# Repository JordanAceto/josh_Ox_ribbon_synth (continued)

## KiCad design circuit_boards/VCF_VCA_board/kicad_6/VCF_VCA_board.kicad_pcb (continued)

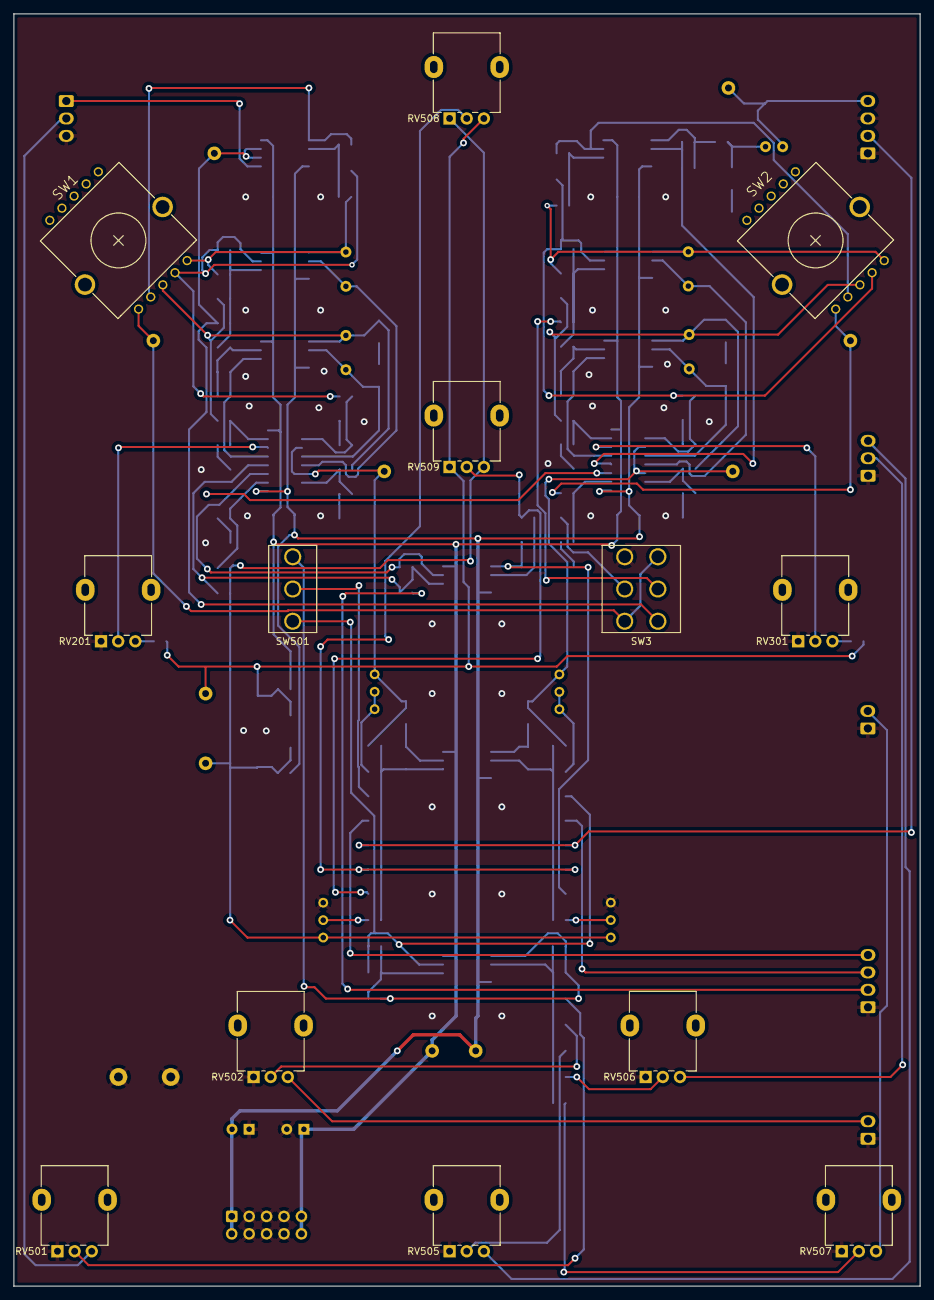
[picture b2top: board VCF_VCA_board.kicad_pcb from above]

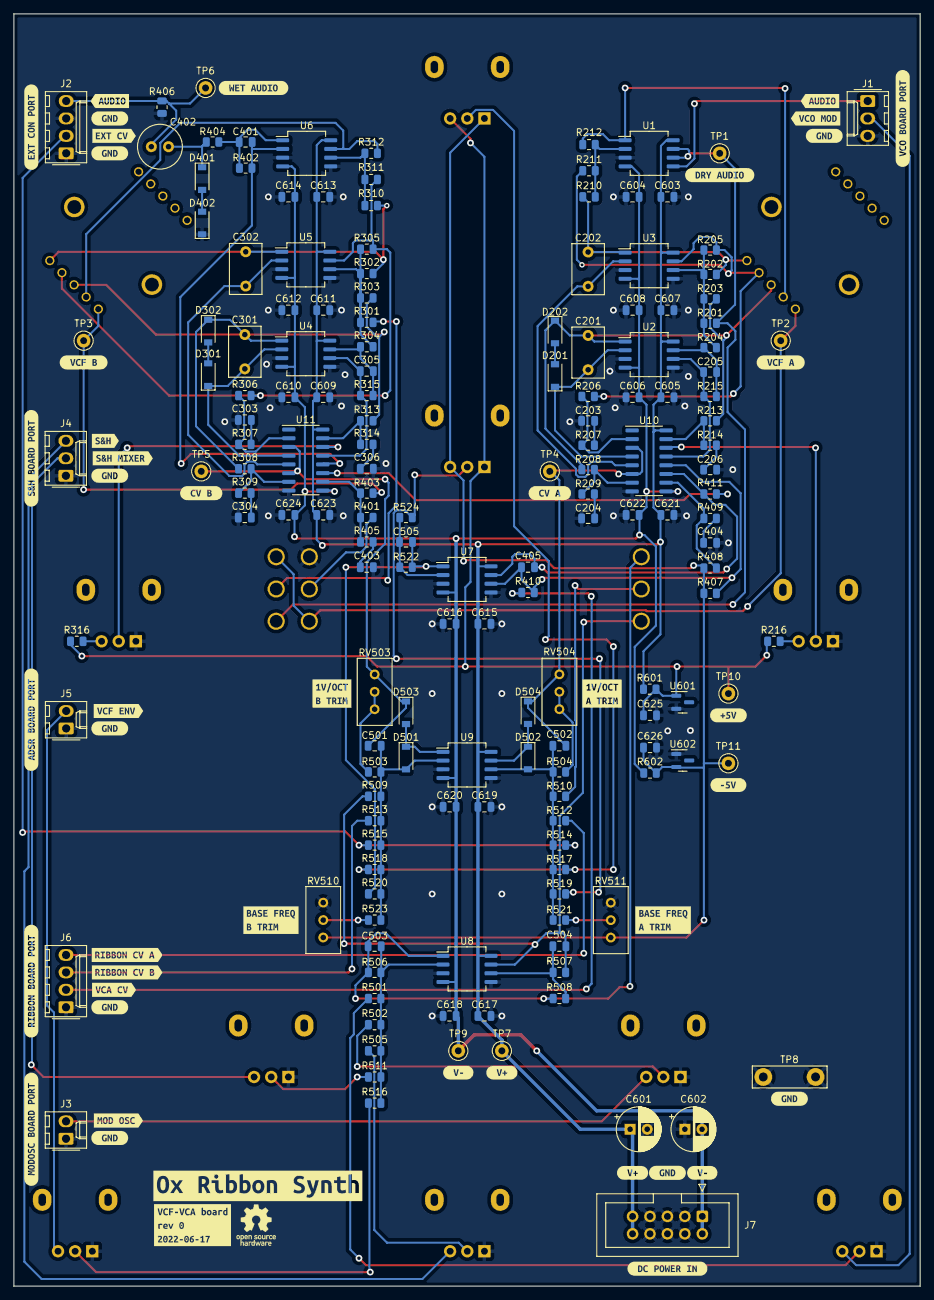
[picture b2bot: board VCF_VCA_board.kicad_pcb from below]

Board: 2 copper layers, 132.1 x 185.4 mm, 220 parts (207 on the bottom side), 94 nets.

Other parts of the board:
C301, C302: 220p; C_Rect_L7.2mm_W4.5mm_P5.00mm_FKS2_FKP2_MKS2_MKP2
C303, C304, C306: 1n2; C_0805_2012Metric
C305: 10p; C_0805_2012Metric
D301, D302: 5v1; D_SOD-123
R301, R302, R304, R305, R306, R308, R310, R311, R312, R315: 30k; R_0805_2012Metric
R303: 390k; R_0805_2012Metric
R307, R309, R314: 220; R_0805_2012Metric
R313: 15k; R_0805_2012Metric
R316: 18k; R_0805_2012Metric
RV301: 10k; Potentiometer_Alpha_RD901F-40-00D_Single_Vertical
kibuzzard-62AC7A9F: G***; kibuzzard-62AC7A9F
kibuzzard-62AC8A1C: G***; kibuzzard-62AC8A1C
kibuzzard-62AC8A2D: G***; kibuzzard-62AC8A2D
kibuzzard-62AC8A4C: G***; kibuzzard-62AC8A4C
kibuzzard-62AC8A9A: G***; kibuzzard-62AC8A9A
kibuzzard-62AC8A40: G***; kibuzzard-62AC8A40
kibuzzard-62AC8A61: G***; kibuzzard-62AC8A61
kibuzzard-62AC8A72: G***; kibuzzard-62AC8A72
kibuzzard-62AC8A87: G***; kibuzzard-62AC8A87
kibuzzard-62AC8B01: G***; kibuzzard-62AC8B01
kibuzzard-62AC8B2D: G***; kibuzzard-62AC8B2D
kibuzzard-62AC8B15: G***; kibuzzard-62AC8B15
kibuzzard-62AC8B47: G***; kibuzzard-62AC8B47
kibuzzard-62AC78CB: G***; kibuzzard-62AC78CB
kibuzzard-62AC88AD: G***; kibuzzard-62AC88AD
kibuzzard-62AC88C6: G***; kibuzzard-62AC88C6
kibuzzard-62AC88DA: G***; kibuzzard-62AC88DA
kibuzzard-62AC88EB: G***; kibuzzard-62AC88EB
kibuzzard-62AC89A8: G***; kibuzzard-62AC89A8
kibuzzard-62AC89C0: G***; kibuzzard-62AC89C0
kibuzzard-62AC89D1: G***; kibuzzard-62AC89D1
kibuzzard-62AC89EA: G***; kibuzzard-62AC89EA
kibuzzard-62AC755C, kibuzzard-62AC755C#2, kibuzzard-62AC755C#3, kibuzzard-62AC755C#4, kibuzzard-62AC755C#5, kibuzzard-62AC755C#6, kibuzzard-62AC755C#7, kibuzzard-62AC755C#8, kibuzzard-62AC755C#9: G***; kibuzzard-62AC755C
kibuzzard-62AC791A, kibuzzard-62AC791A#2: G***; kibuzzard-62AC791A
kibuzzard-62AC792A, kibuzzard-62AC792A#2: G***; kibuzzard-62AC792A
kibuzzard-62AC886F: G***; kibuzzard-62AC886F
kibuzzard-62AC887D: G***; kibuzzard-62AC887D
kibuzzard-62AC892A, kibuzzard-62AC892A#2: G***; kibuzzard-62AC892A
kibuzzard-62AC8760: G***; kibuzzard-62AC8760
kibuzzard-62AC8892: G***; kibuzzard-62AC8892
kibuzzard-62AC8908: G***; kibuzzard-62AC8908
kibuzzard-62AC8951: G***; kibuzzard-62AC8951
kibuzzard-62AC8974: G***; kibuzzard-62AC8974
kibuzzard-62AC8994: G***; kibuzzard-62AC8994

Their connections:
+5V REF: R316.1; also elsewhere on the board
/SVF_B/BP_OUT: C301.2, D302.1 (K), R303.2, R308.1, R313.2; also elsewhere on the board
/SVF_B/HP_OUT: R305.2, R306.1, R311.1; also elsewhere on the board
/SVF_B/LP_OUT: C302.2, R302.2, R310.1; also elsewhere on the board
/SVF_B/NOTCH_OUT: R312.2; also elsewhere on the board
/SVF_B/SIGNAL_IN: R301.1; also elsewhere on the board
unnamed 35: C301.1, D301.1 (K); also elsewhere on the board
unnamed 36: C302.1; also elsewhere on the board
unnamed: C303.1, R307.2
unnamed: C304.1, R309.2
unnamed 39: C305.1, R304.2, R315.2; also elsewhere on the board
unnamed 40: C305.2, R315.1; also elsewhere on the board
unnamed: C306.1, R314.2
unnamed: D301.2 (A), D302.2 (A)
unnamed 69: R301.2, R302.1, R303.1, R304.1, R305.1; also elsewhere on the board
unnamed 70: R306.2, R307.1; also elsewhere on the board
unnamed 71: R308.2, R309.1; also elsewhere on the board
unnamed 72: R310.2, R311.2, R312.1; also elsewhere on the board
unnamed 73: R313.1, R314.1; also elsewhere on the board
unnamed: R316.2, RV301.3
unnamed 91: RV301.2; also elsewhere on the board

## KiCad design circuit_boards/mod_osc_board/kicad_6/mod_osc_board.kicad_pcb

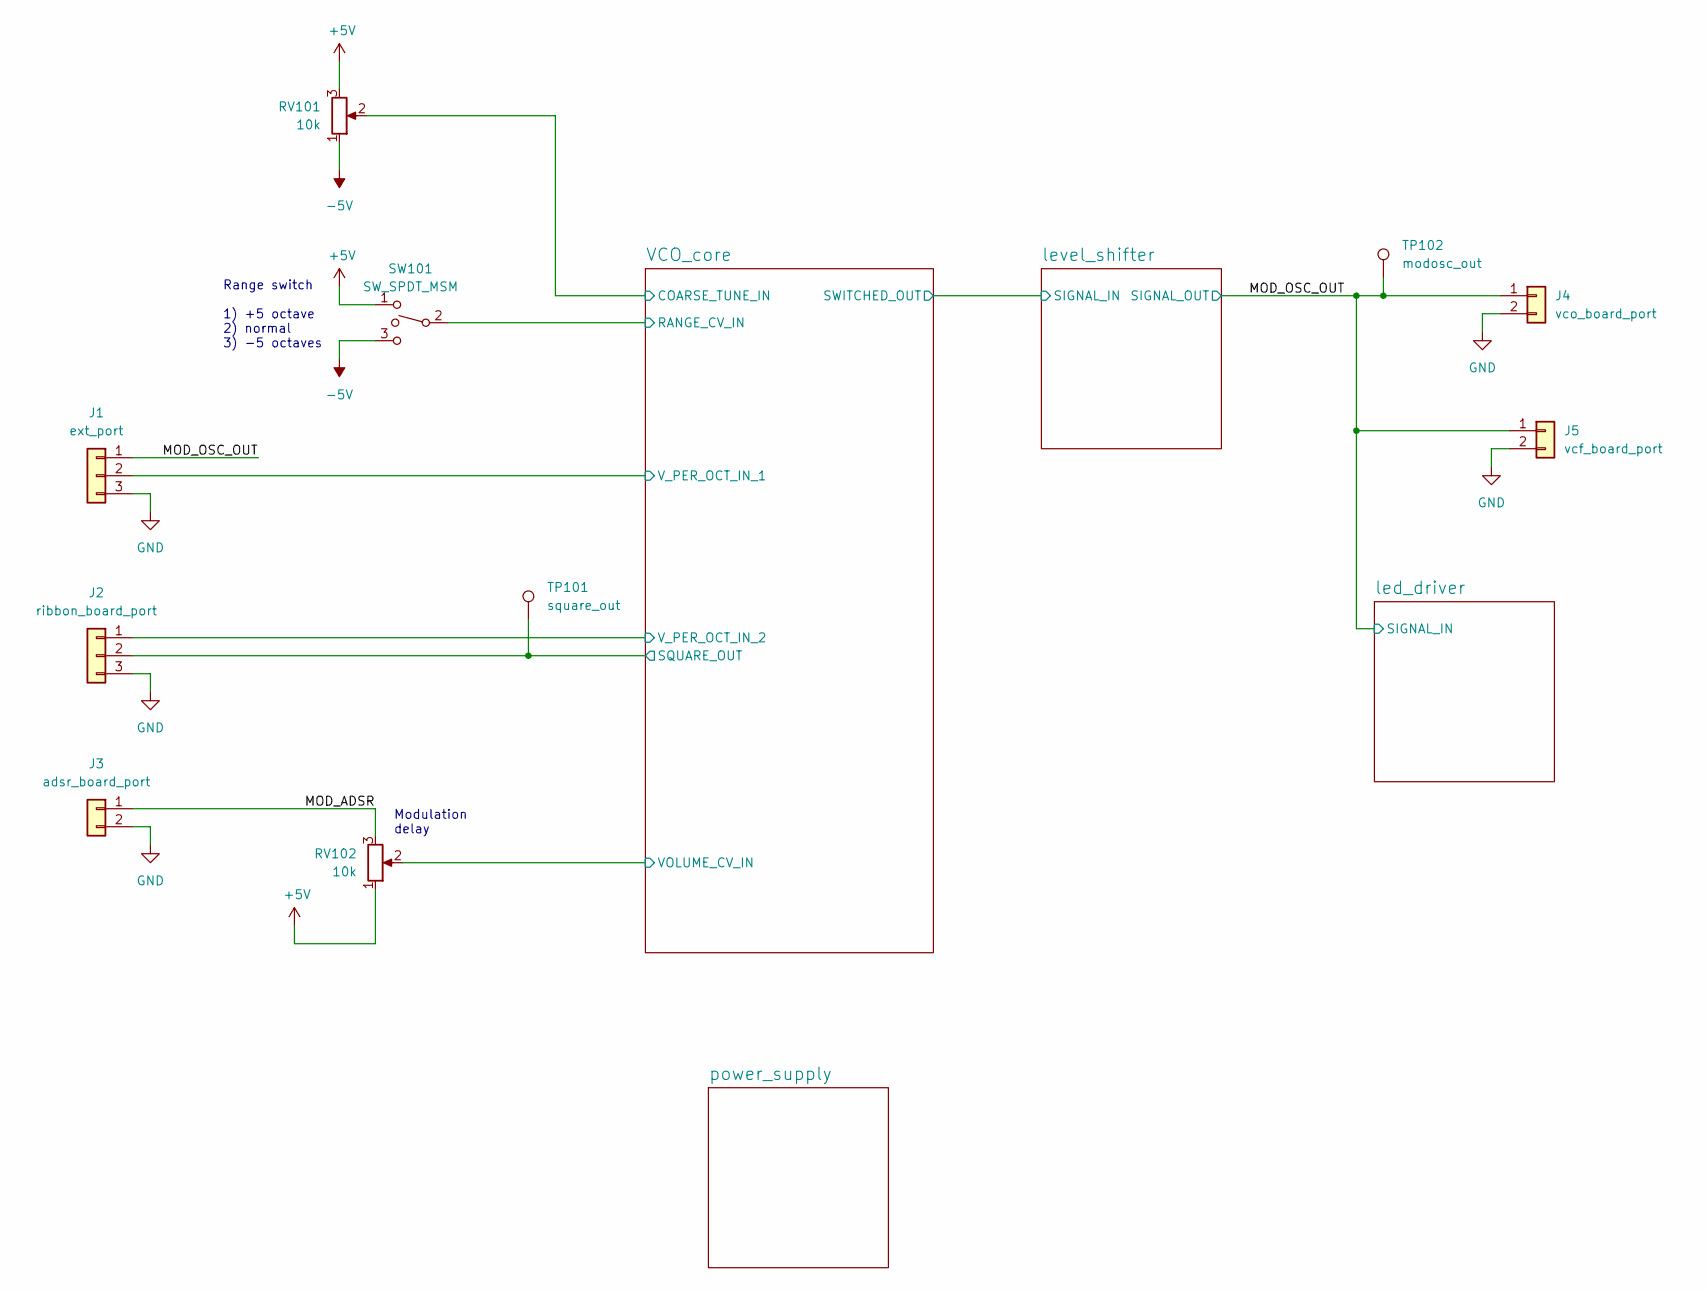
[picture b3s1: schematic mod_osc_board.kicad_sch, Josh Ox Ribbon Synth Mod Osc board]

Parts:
J1: ext_port; Molex_KK-254_AE-6410-03A_1x03_P2.54mm_Vertical
J2: ribbon_board_port; Molex_KK-254_AE-6410-03A_1x03_P2.54mm_Vertical
J3: adsr_board_port; Molex_KK-254_AE-6410-02A_1x02_P2.54mm_Vertical
J4: vco_board_port; Molex_KK-254_AE-6410-02A_1x02_P2.54mm_Vertical
J5: vcf_board_port; Molex_KK-254_AE-6410-02A_1x02_P2.54mm_Vertical
RV101, RV102: 10k; Potentiometer_P260T
SW101: SW_SPDT_MSM; SPDT_mini_toggle
TP101: square_out; TestPoint_Keystone_5000-5004_Miniature
TP102: modosc_out; TestPoint_Keystone_5000-5004_Miniature

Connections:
+5V: RV101.3, RV102.1, SW101.1; also elsewhere on the board
-5V: RV101.1, SW101.3; also elsewhere on the board
/MOD_ADSR: J3.1, RV102.3
/MOD_OSC_OUT: J1.1, J4.1, J5.1, TP102.1; also elsewhere on the board
/VCO_core/COARSE_TUNE_IN: RV101.2; also elsewhere on the board
/VCO_core/RANGE_CV_IN: SW101.2; also elsewhere on the board
/VCO_core/SQUARE_OUT: J2.2, TP101.1; also elsewhere on the board
/VCO_core/VOLUME_CV_IN: RV102.2; also elsewhere on the board
/VCO_core/V_PER_OCT_IN_1: J1.2; also elsewhere on the board
/VCO_core/V_PER_OCT_IN_2: J2.1; also elsewhere on the board

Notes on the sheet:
Range switch 1) +5 octave 2) normal 3) -5 octaves
Modulation delay

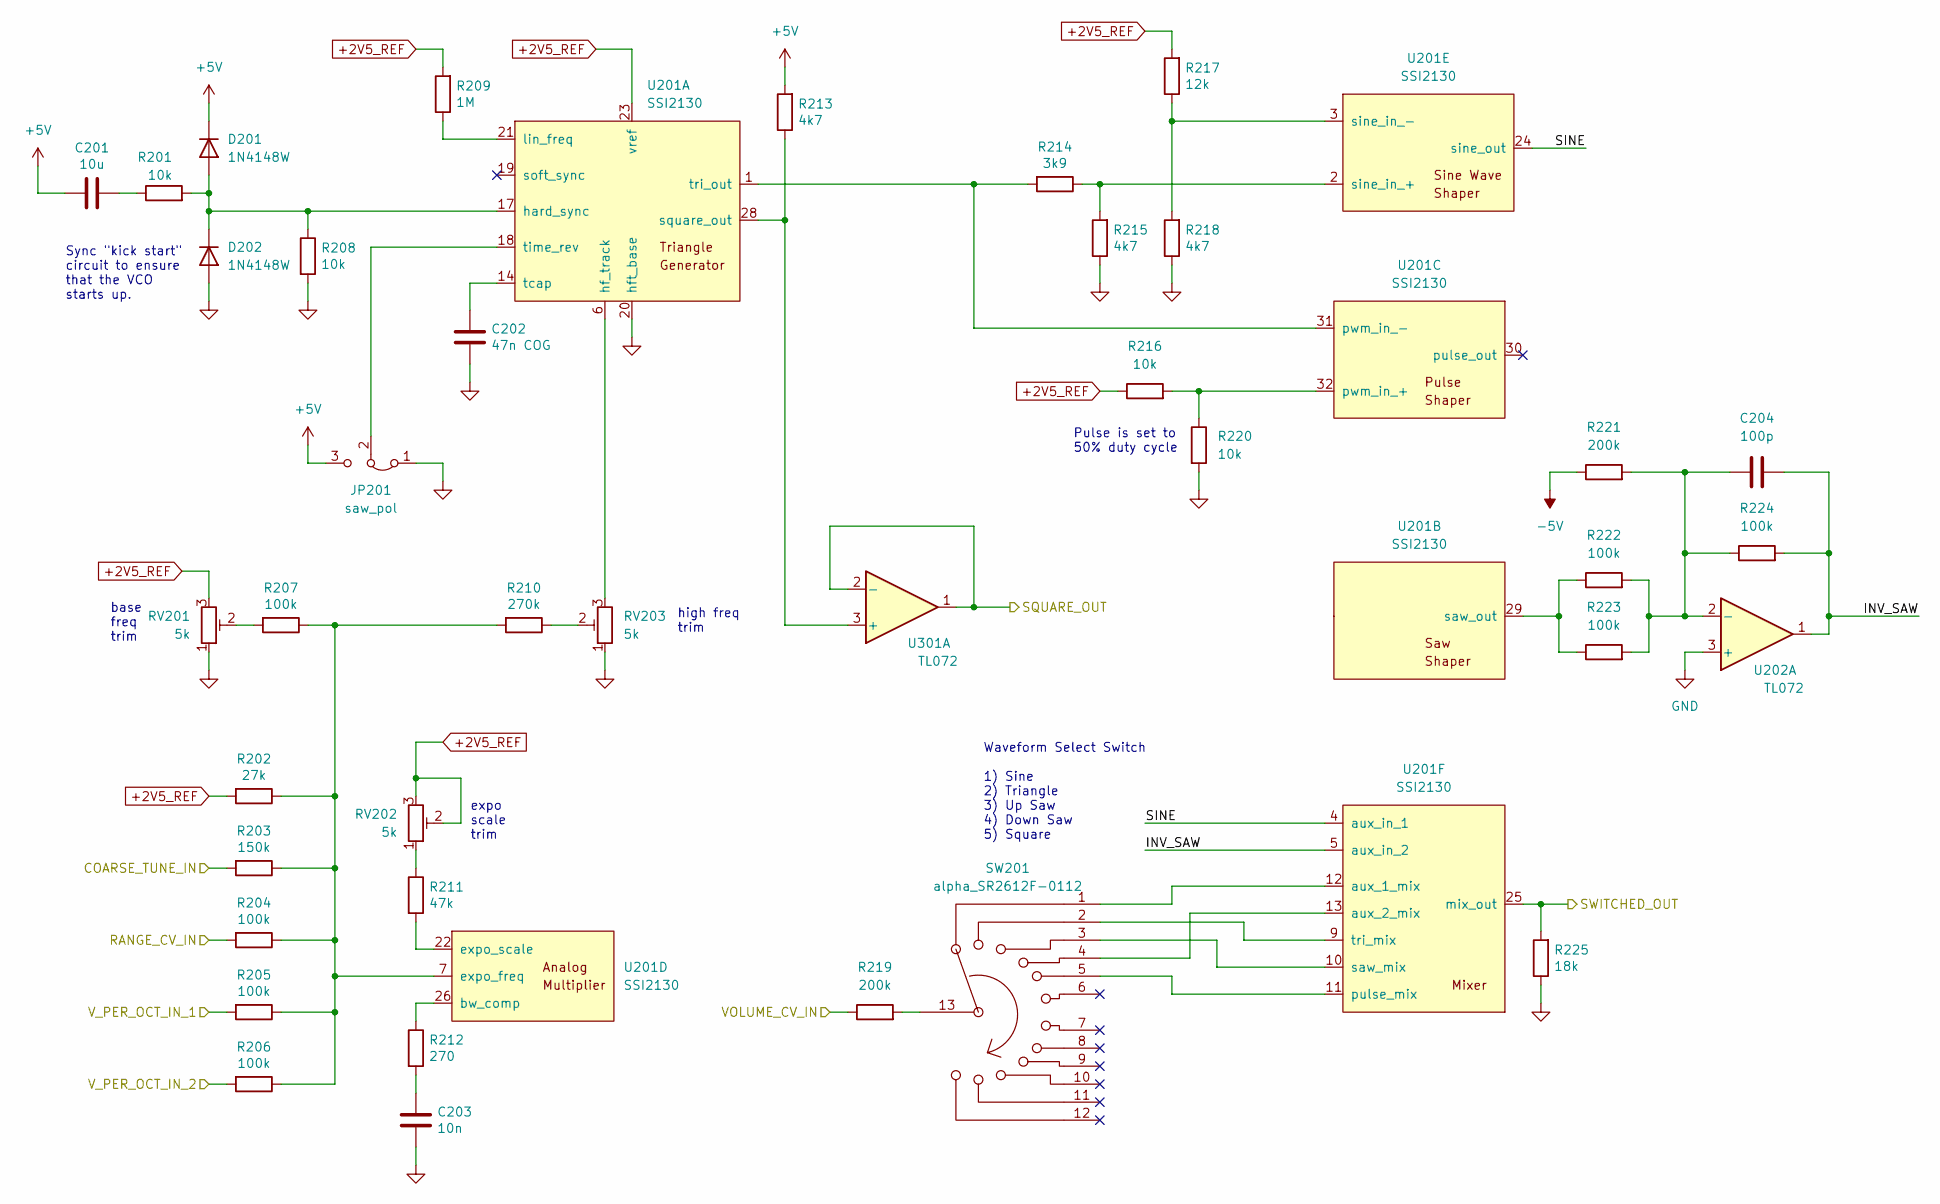
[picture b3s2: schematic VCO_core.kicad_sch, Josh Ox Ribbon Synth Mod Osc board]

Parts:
C201: 10u; C_0805_2012Metric
C202: 47n COG; C_0805_2012Metric
C203: 10n; C_0805_2012Metric
C204: 100p; C_0805_2012Metric
D201, D202: 1N4148W; D_SOD-123
JP201: saw_pol; SolderJumper-3_P1.3mm_Bridged12_RoundedPad1.0x1.5mm
R201, R208, R216, R220: 10k; R_0805_2012Metric
R202: 27k; R_0805_2012Metric
R203: 150k; R_0805_2012Metric
R204, R205, R206, R207, R222, R223, R224: 100k; R_0805_2012Metric
R209: 1M; R_0805_2012Metric
R210: 270k; R_0805_2012Metric
R211: 47k; R_0805_2012Metric
R212: 270; R_0805_2012Metric
R213, R215, R218: 4k7; R_0805_2012Metric
R214: 3k9; R_0805_2012Metric
R217: 12k; R_0805_2012Metric
R219, R221: 200k; R_0805_2012Metric
R225: 18k; R_0805_2012Metric
RV201, RV202, RV203: 5k; Potentiometer_Bourns_3296W_Vertical
SW201: alpha_SR2612F-0112; apha_SR2612F-0112
U201: SSI2130; PQN32_HandSoldering
U202, U301: TL072; SO-8_5.3x6.2mm_P1.27mm

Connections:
+2V5_REF: R202.2, R209.2, R216.1, R217.2, RV201.3, RV202.2, RV202.3, U201.23 (vref); also elsewhere on the board
+5V: C201.2, D201.1 (K), JP201.3 (B), R213.2; also elsewhere on the board
-5V: R221.1; also elsewhere on the board
/VCO_core/COARSE_TUNE_IN: R203.2; also elsewhere on the board
/VCO_core/INV_SAW: C204.2, R224.2, U201.5 (aux_in_2), U202.1
/VCO_core/RANGE_CV_IN: R204.2; also elsewhere on the board
/VCO_core/SINE: U201.4 (aux_in_1), U201.24 (sine_out)
/VCO_core/SQUARE_OUT: U301.1, U301.2 (-); also elsewhere on the board
/VCO_core/SWITCHED_OUT: R225.2, U201.25 (mix_out); also elsewhere on the board
/VCO_core/VOLUME_CV_IN: R219.1; also elsewhere on the board
/VCO_core/V_PER_OCT_IN_1: R205.2; also elsewhere on the board
/VCO_core/V_PER_OCT_IN_2: R206.2; also elsewhere on the board
unnamed: C201.1, R201.1
unnamed: C202.1, U201.14 (tcap)
unnamed: C203.1, R212.2
unnamed: C204.1, R221.2, R222.2, R223.2, R224.1, U202.2 (-)
unnamed: D201.2 (A), D202.1 (K), R201.2, R208.1, U201.17 (hard_sync)
unnamed: JP201.2 (C), U201.18 (time_rev)
unnamed: R202.1, R203.1, R204.1, R205.1, R206.1, R207.1, R210.2, U201.7 (expo_freq)
unnamed: R207.2, RV201.2
unnamed: R209.1, U201.21 (lin_freq)
unnamed: R210.1, RV203.2
unnamed: R211.1, RV202.1
unnamed: R211.2, U201.22 (expo_scale)
unnamed: R212.1, U201.26 (bw_comp)
unnamed: R213.1, U201.28 (square_out), U301.3 (+)
unnamed: R214.1, R215.2, U201.2 (sine_in_+)
unnamed: R214.2, U201.1 (tri_out), U201.31 (pwm_in_-)
unnamed: R216.2, R220.1, U201.32 (pwm_in_+)
unnamed: R217.1, R218.2, U201.3 (sine_in_-)
unnamed: R219.2, SW201.13
unnamed: R222.1, R223.1, U201.29 (saw_out)
unnamed: RV203.3, U201.6 (hf_track)
unnamed: SW201.1, U201.12 (aux_1_mix)
unnamed: SW201.2, U201.9 (tri_mix)
unnamed: SW201.3, U201.10 (saw_mix)
unnamed: SW201.4, U201.13 (aux_2_mix)
unnamed: SW201.5, U201.11 (pulse_mix)

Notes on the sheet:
Waveform Select Switch 1) Sine 2) Triangle 3) Up Saw 4) Down Saw 5) Square
high freq trim
Pulse is set to 50% duty cycle
expo scale trim
Sync "kick start" circuit to ensure that the VCO starts up.
base freq trim

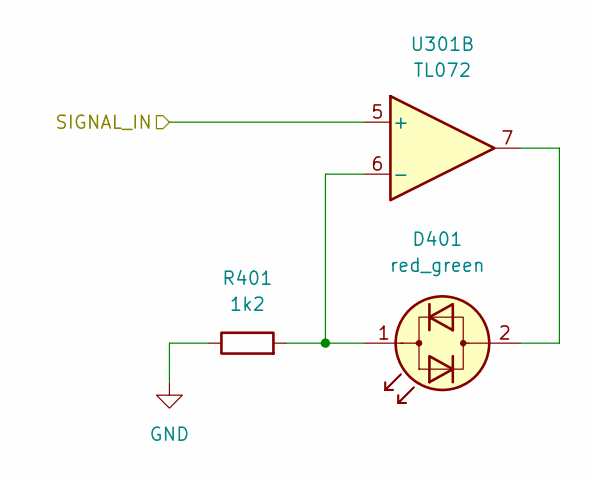
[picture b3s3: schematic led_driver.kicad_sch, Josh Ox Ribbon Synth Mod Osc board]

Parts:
D401: red_green; LED_D5.0mm
R401: 1k2; R_0805_2012Metric
U301: TL072; SO-8_5.3x6.2mm_P1.27mm

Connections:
/MOD_OSC_OUT: U301.5 (+); also elsewhere on the board
unnamed 22: D401.1 (KA), R401.2, U301.6 (-); also elsewhere on the board
unnamed 23: D401.2 (AK), U301.7; also elsewhere on the board

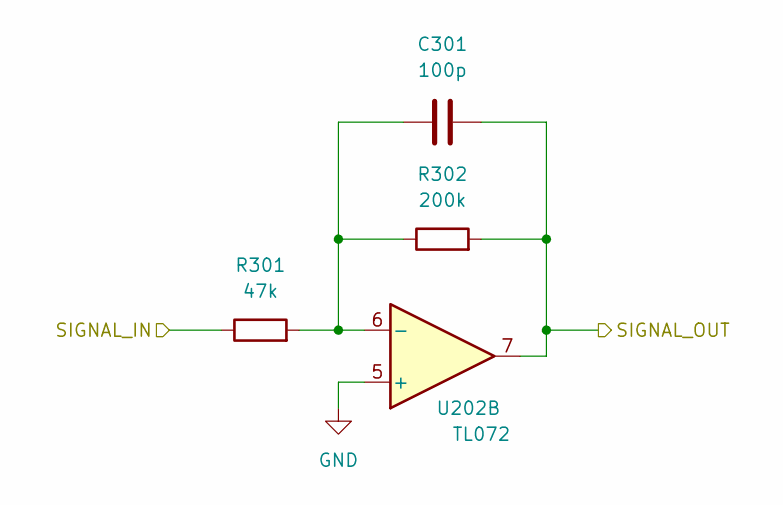
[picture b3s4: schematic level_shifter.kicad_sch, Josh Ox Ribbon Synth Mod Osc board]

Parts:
C301: 100p; C_0805_2012Metric
R301: 47k; R_0805_2012Metric
R302: 200k; R_0805_2012Metric
U202: TL072; SO-8_5.3x6.2mm_P1.27mm

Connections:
/MOD_OSC_OUT: C301.2, R302.2, U202.7; also elsewhere on the board
/VCO_core/SWITCHED_OUT: R301.1; also elsewhere on the board
unnamed: C301.1, R301.2, R302.1, U202.6 (-)

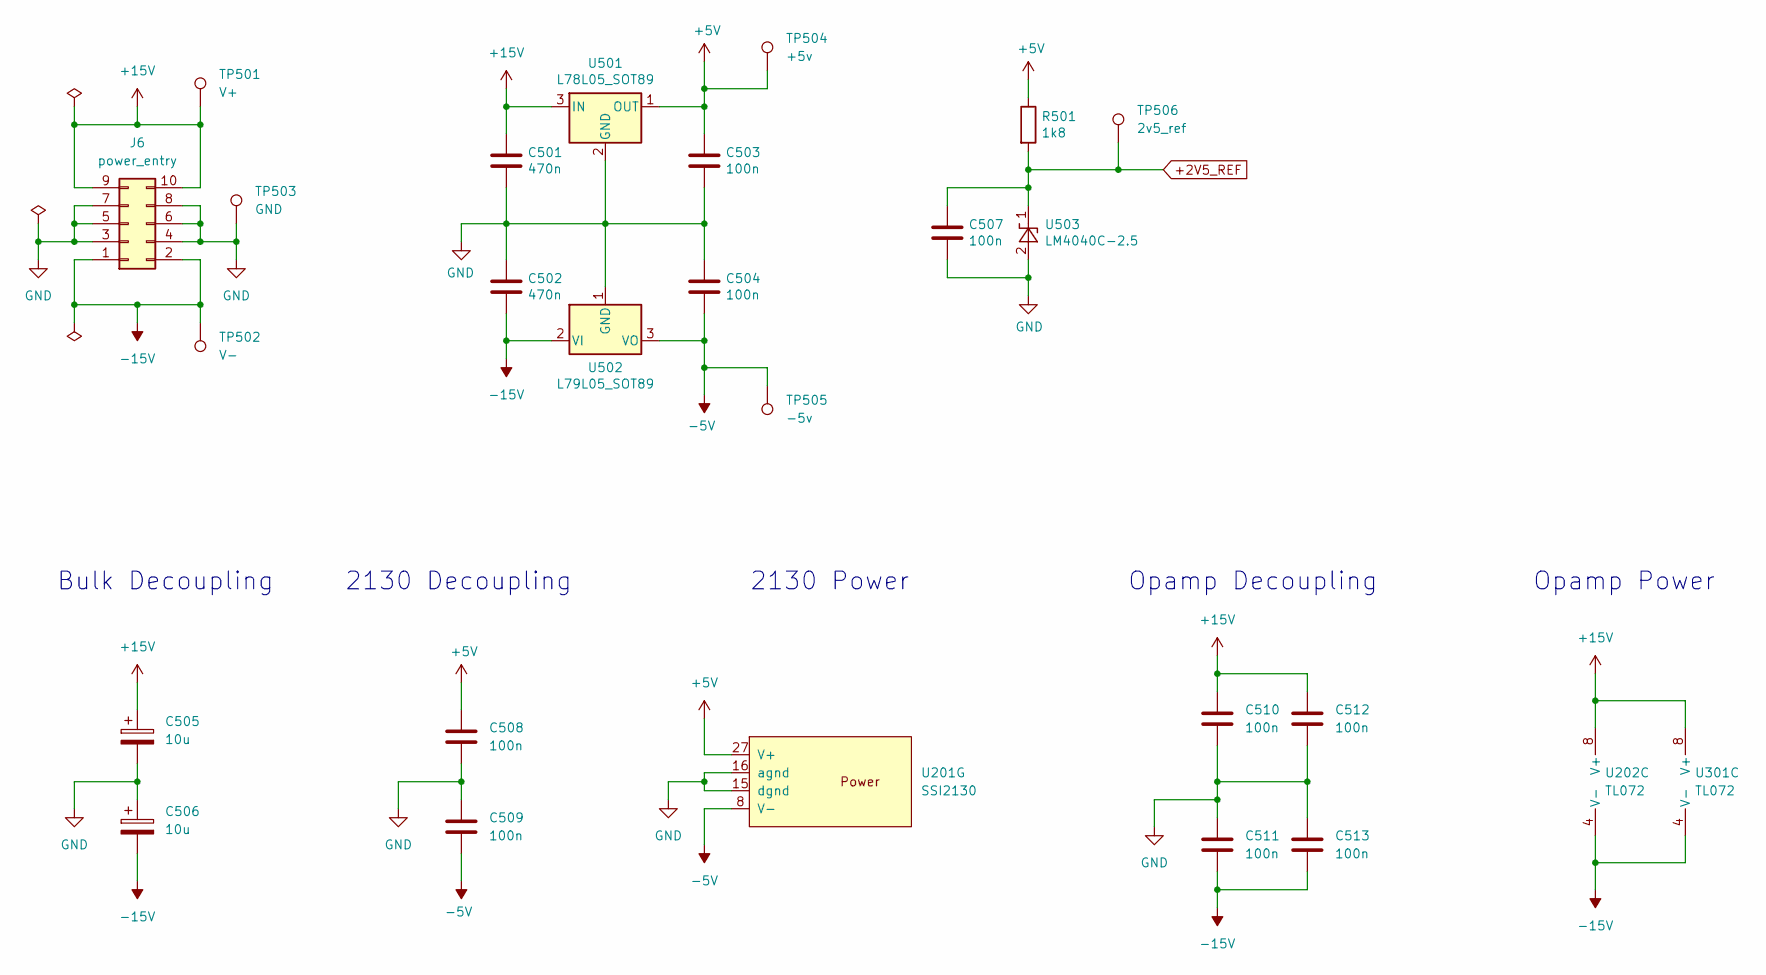
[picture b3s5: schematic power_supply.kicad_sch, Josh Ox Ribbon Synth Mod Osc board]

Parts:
C501, C502: 470n; C_0805_2012Metric
C503, C504, C507, C508, C509, C510, C511, C512, C513: 100n; C_0805_2012Metric
C505, C506: 10u; CP_Radial_D6.3mm_P2.50mm
J6: power_entry; IDC-Header_2x05_P2.54mm_Vertical
R501: 1k8; R_0805_2012Metric
TP501: V+; TestPoint_Keystone_5000-5004_Miniature
TP502: V-; TestPoint_Keystone_5000-5004_Miniature
TP503: GND; TestPoint_Bridge_Pitch7.62mm_Drill1.3mm
TP504: +5v; TestPoint_Keystone_5000-5004_Miniature
TP505: -5v; TestPoint_Keystone_5000-5004_Miniature
TP506: 2v5_ref; TestPoint_Keystone_5000-5004_Miniature
U201: SSI2130; PQN32_HandSoldering
U202, U301: TL072; SO-8_5.3x6.2mm_P1.27mm
U501: L78L05_SOT89; SOT-89-3
U502: L79L05_SOT89; SOT-89-3
U503: LM4040C-2.5; SOT-23

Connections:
+2V5_REF: C507.1, R501.2, TP506.1, U503.1 (K); also elsewhere on the board
+5V: C503.1, C508.1, R501.1, TP504.1, U201.27 (V+), U501.1 (OUT); also elsewhere on the board
+15V: C501.1, C505.1, C510.1, C512.1, J6.9, J6.10, TP501.1, U202.8 (V+), U301.8 (V+), U501.3 (IN)
-5V: C504.2, C509.2, TP505.1, U201.8 (V-), U502.3 (VO); also elsewhere on the board
-15V: C502.2, C506.2, C511.2, C513.2, J6.1, J6.2, TP502.1, U202.4 (V-), U301.4 (V-), U502.2 (VI)

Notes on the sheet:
2130 Decoupling
Opamp Decoupling
2130 Power
Opamp Power
Bulk Decoupling

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
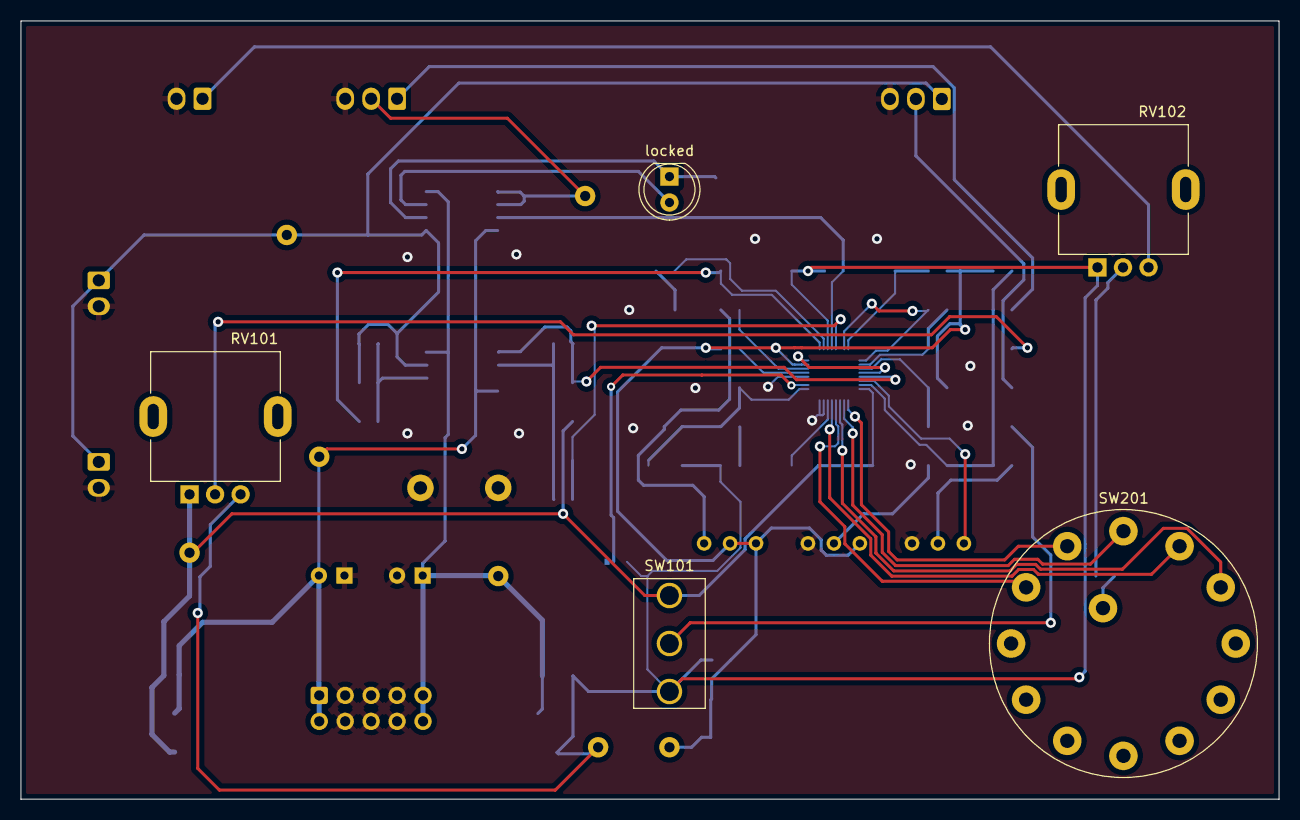
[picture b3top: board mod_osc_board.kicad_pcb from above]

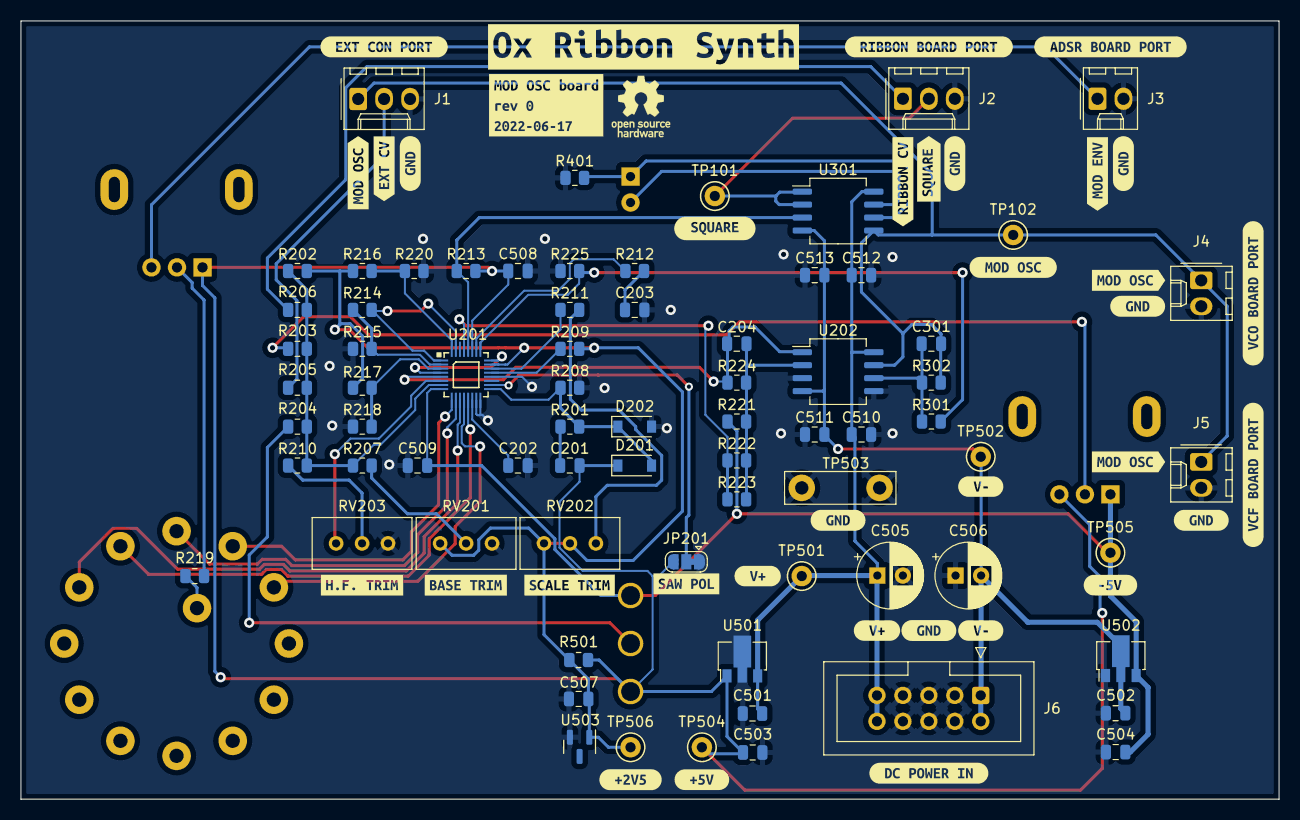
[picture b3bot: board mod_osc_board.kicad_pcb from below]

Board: 2 copper layers, 123.2 x 76.2 mm, 113 parts (108 on the bottom side), 46 nets.

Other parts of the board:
kibuzzard-62AC7A9F: G***; kibuzzard-62AC7A9F
kibuzzard-62AC7C76, kibuzzard-62AC7C76#2, kibuzzard-62AC7C76#3: G***; kibuzzard-62AC7C76
kibuzzard-62AC7CCE: G***; kibuzzard-62AC7CCE
kibuzzard-62AC7CEB: G***; kibuzzard-62AC7CEB
kibuzzard-62AC7D00: G***; kibuzzard-62AC7D00
kibuzzard-62AC7D1D: G***; kibuzzard-62AC7D1D
kibuzzard-62AC7D8B: G***; kibuzzard-62AC7D8B
kibuzzard-62AC7D30: G***; kibuzzard-62AC7D30
kibuzzard-62AC7D44: G***; kibuzzard-62AC7D44
kibuzzard-62AC7D55: G***; kibuzzard-62AC7D55
kibuzzard-62AC7D68: G***; kibuzzard-62AC7D68
kibuzzard-62AC7D79: G***; kibuzzard-62AC7D79
kibuzzard-62AC7DA9: G***; kibuzzard-62AC7DA9
kibuzzard-62AC7DB6: G***; kibuzzard-62AC7DB6
kibuzzard-62AC7DF7: G***; kibuzzard-62AC7DF7
kibuzzard-62AC7EA8: G***; kibuzzard-62AC7EA8
kibuzzard-62AC7EE1: G***; kibuzzard-62AC7EE1
kibuzzard-62AC7EFA: G***; kibuzzard-62AC7EFA
kibuzzard-62AC7F0B: G***; kibuzzard-62AC7F0B
kibuzzard-62AC78CB: G***; kibuzzard-62AC78CB
kibuzzard-62AC755C, kibuzzard-62AC755C#2, kibuzzard-62AC755C#3, kibuzzard-62AC755C#4, kibuzzard-62AC755C#5, kibuzzard-62AC755C#6, kibuzzard-62AC755C#7: G***; kibuzzard-62AC755C
kibuzzard-62AC791A, kibuzzard-62AC791A#2: G***; kibuzzard-62AC791A
kibuzzard-62AC792A, kibuzzard-62AC792A#2: G***; kibuzzard-62AC792A
kibuzzard-62AC911A: G***; kibuzzard-62AC911A
kibuzzard-62ACB089: G***; kibuzzard-62ACB089
locked: red_green; LED_D5.0mm

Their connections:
unnamed 22: locked.1 (KA); also elsewhere on the board
unnamed 23: locked.2 (AK); also elsewhere on the board

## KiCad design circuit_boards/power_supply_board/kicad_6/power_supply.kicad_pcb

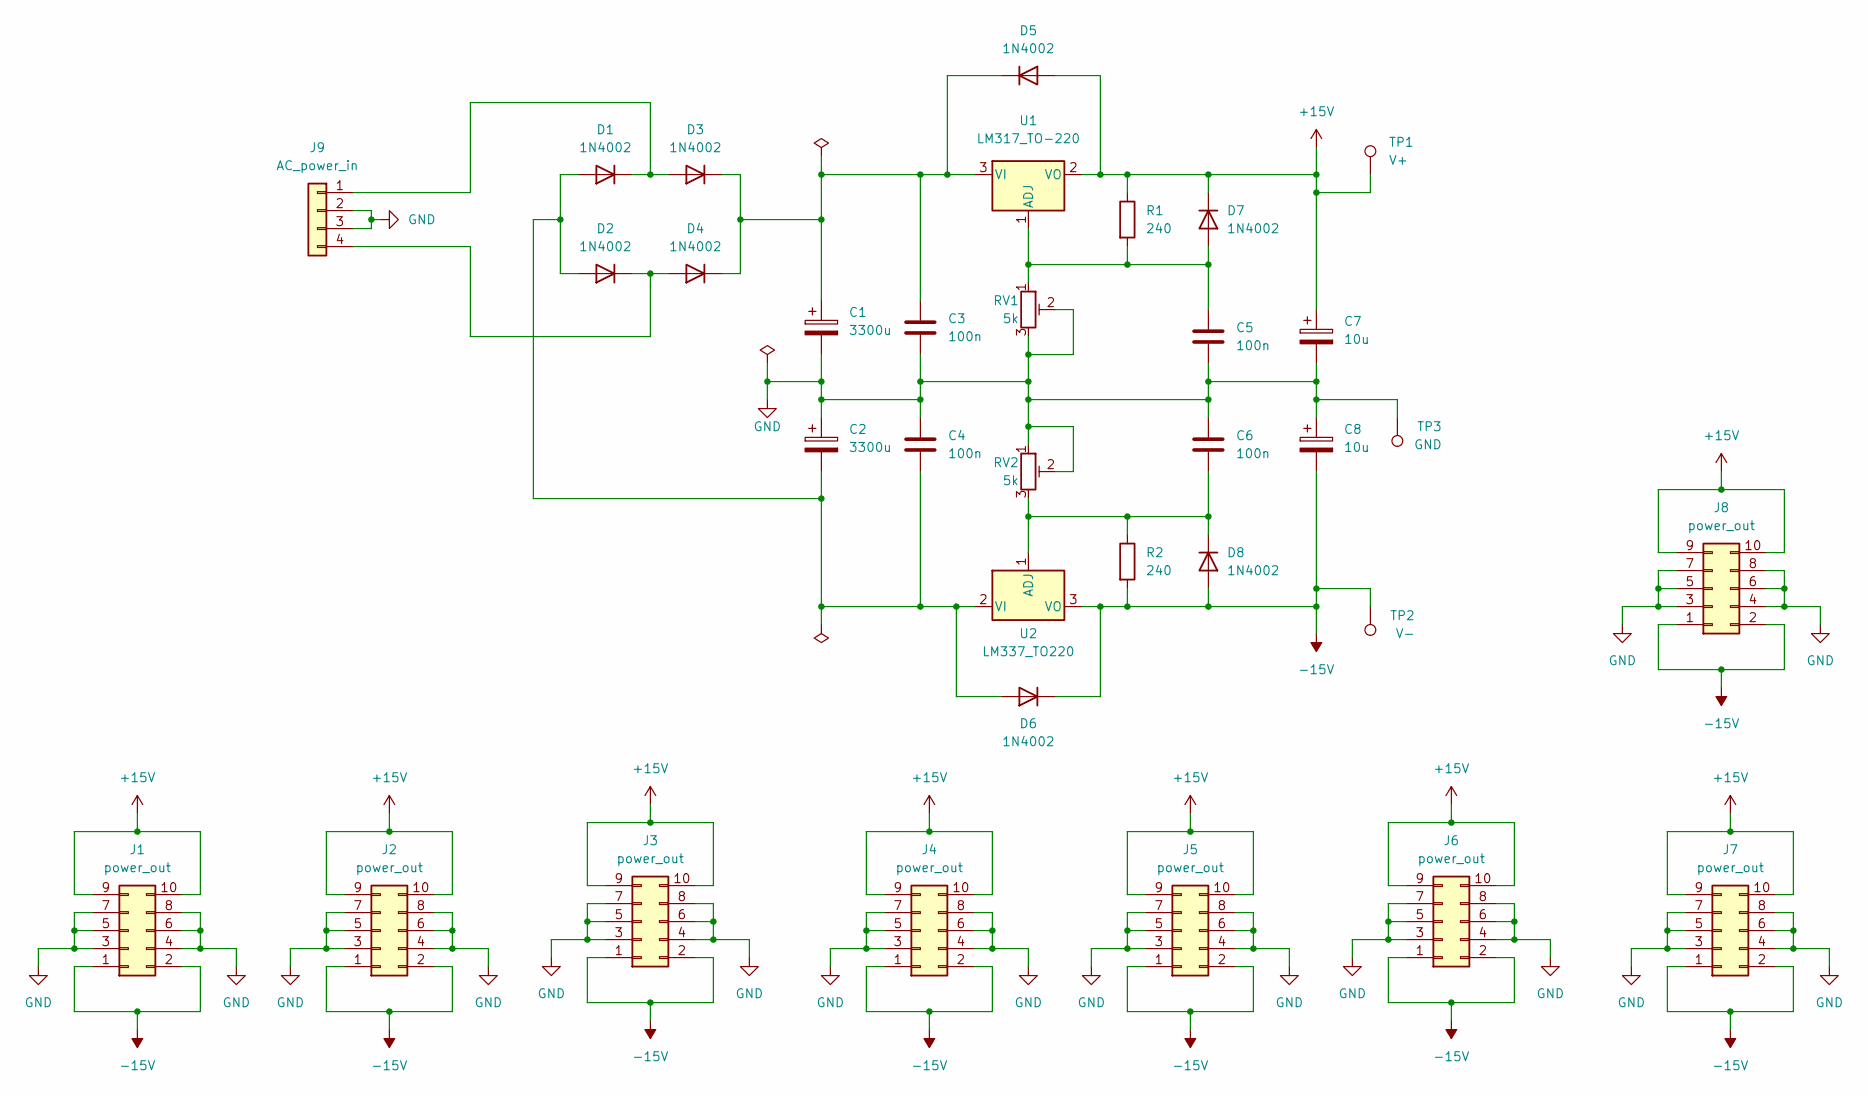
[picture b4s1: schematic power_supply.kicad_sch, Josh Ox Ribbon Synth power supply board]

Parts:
C1, C2: 3300u; CP_Radial_D18.0mm_P7.50mm
C3, C4, C5, C6: 100n; C_Rect_L7.0mm_W2.5mm_P5.00mm
C7, C8: 10u; CP_Radial_D6.3mm_P2.50mm
D1, D2, D3, D4, D5, D6, D7, D8: 1N4002; D_DO-41_SOD81_P10.16mm_Horizontal
J1, J2, J3, J4, J5, J6, J7, J8: power_out; IDC-Header_2x05_P2.54mm_Vertical
J9: AC_power_in; Molex_Mini-Fit_Jr_5566-04A_2x02_P4.20mm_Vertical
R1, R2: 240; R_Axial_DIN0207_L6.3mm_D2.5mm_P10.16mm_Horizontal
RV1, RV2: 5k; Potentiometer_Bourns_3296W_Vertical
TP1: V+; TestPoint_Keystone_5000-5004_Miniature
TP2: V-; TestPoint_Keystone_5000-5004_Miniature
TP3: GND; TestPoint_Bridge_Pitch7.62mm_Drill1.3mm
U1: LM317_TO-220; TO-220-3_Vertical
U2: LM337_TO220; TO-220-3_Vertical

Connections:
+15V: C7.1, D5.2 (A), D7.1 (K), J1.9, J1.10, J2.9, J2.10, J3.9, J3.10, J4.9, J4.10, J5.9, J5.10, J6.9, J6.10, J7.9, J7.10, J8.9, J8.10, R1.1, TP1.1, U1.2 (VO)
-15V: C8.2, D6.1 (K), D8.2 (A), J1.1, J1.2, J2.1, J2.2, J3.1, J3.2, J4.1, J4.2, J5.1, J5.2, J6.1, J6.2, J7.1, J7.2, J8.1, J8.2, R2.2, TP2.1, U2.3 (VO)
GND: C1.2, C2.1, C3.2, C4.1, C5.2, C6.1, C7.2, C8.1, J1.3, J1.4, J1.5, J1.6, J1.7, J1.8, J2.3, J2.4, J2.5, J2.6, J2.7, J2.8, J3.3, J3.4, J3.5, J3.6, J3.7, J3.8, J4.3, J4.4, J4.5, J4.6, J4.7, J4.8, J5.3, J5.4, J5.5, J5.6, J5.7, J5.8, J6.3, J6.4, J6.5, J6.6, J6.7, J6.8, J7.3, J7.4, J7.5, J7.6, J7.7, J7.8, J8.3, J8.4, J8.5, J8.6, J8.7, J8.8, J9.2, J9.3, RV1.2, RV1.3, RV2.1, RV2.2, TP3.1
unnamed: C1.1, C3.1, D3.1 (K), D4.1 (K), D5.1 (K), U1.3 (VI)
unnamed: C2.2, C4.2, D1.2 (A), D2.2 (A), D6.2 (A), U2.2 (VI)
unnamed: C5.1, D7.2 (A), R1.2, RV1.1, U1.1 (ADJ)
unnamed: C6.2, D8.1 (K), R2.1, RV2.3, U2.1 (ADJ)
unnamed: D1.1 (K), D3.2 (A), J9.1
unnamed: D2.1 (K), D4.2 (A), J9.4

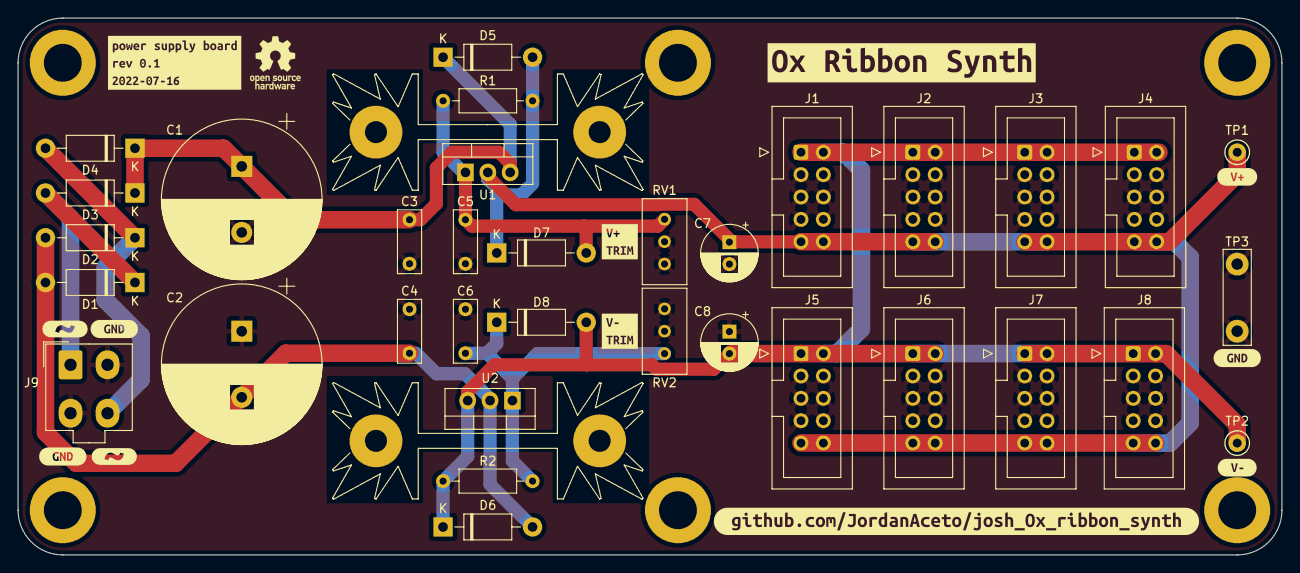
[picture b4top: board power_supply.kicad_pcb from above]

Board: 2 copper layers, 143.5 x 61.0 mm, 46 parts (0 on the bottom side), 9 nets.

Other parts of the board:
kibuzzard-62AC7A9F: G***; kibuzzard-62AC7A9F
kibuzzard-62B8A02A, kibuzzard-62B8A02A#2: G***; kibuzzard-62B8A02A
kibuzzard-62B8A297: G***; kibuzzard-62B8A297
kibuzzard-62B89F9F: G***; kibuzzard-62B89F9F
kibuzzard-62B89F93, kibuzzard-62B89F93#2, kibuzzard-62B89F93#3: G***; kibuzzard-62B89F93
kibuzzard-62B89FA9: G***; kibuzzard-62B89FA9
kibuzzard-62B89FC4: G***; kibuzzard-62B89FC4
kibuzzard-62B89FD2: G***; kibuzzard-62B89FD2
kibuzzard-62D2BBF1: G***; kibuzzard-62D2BBF1
